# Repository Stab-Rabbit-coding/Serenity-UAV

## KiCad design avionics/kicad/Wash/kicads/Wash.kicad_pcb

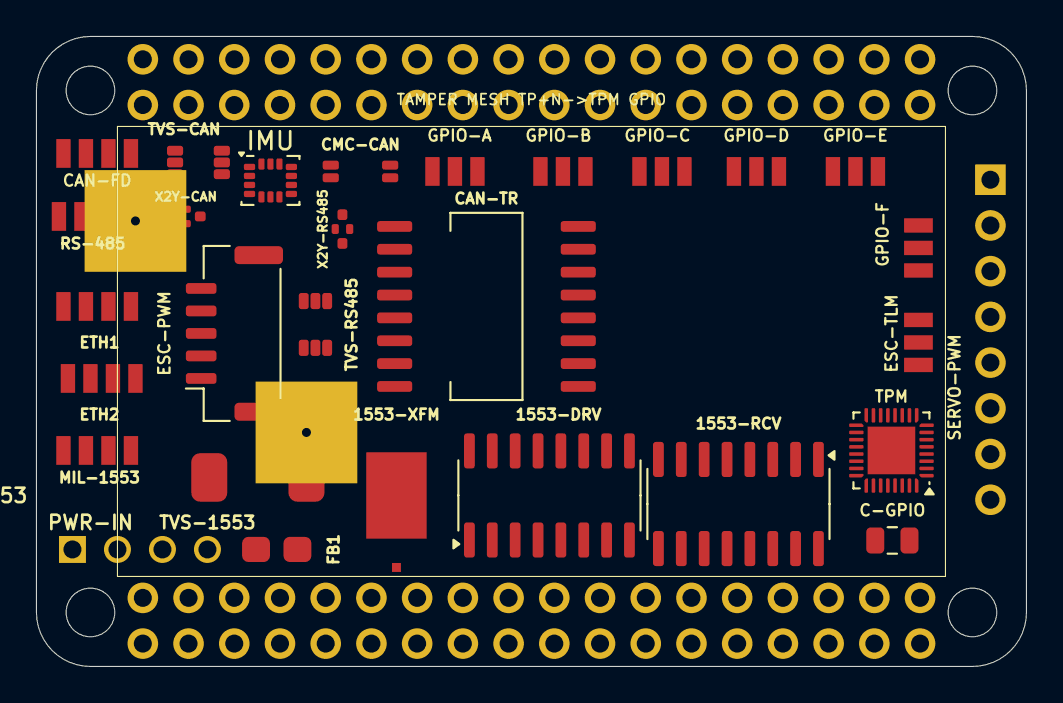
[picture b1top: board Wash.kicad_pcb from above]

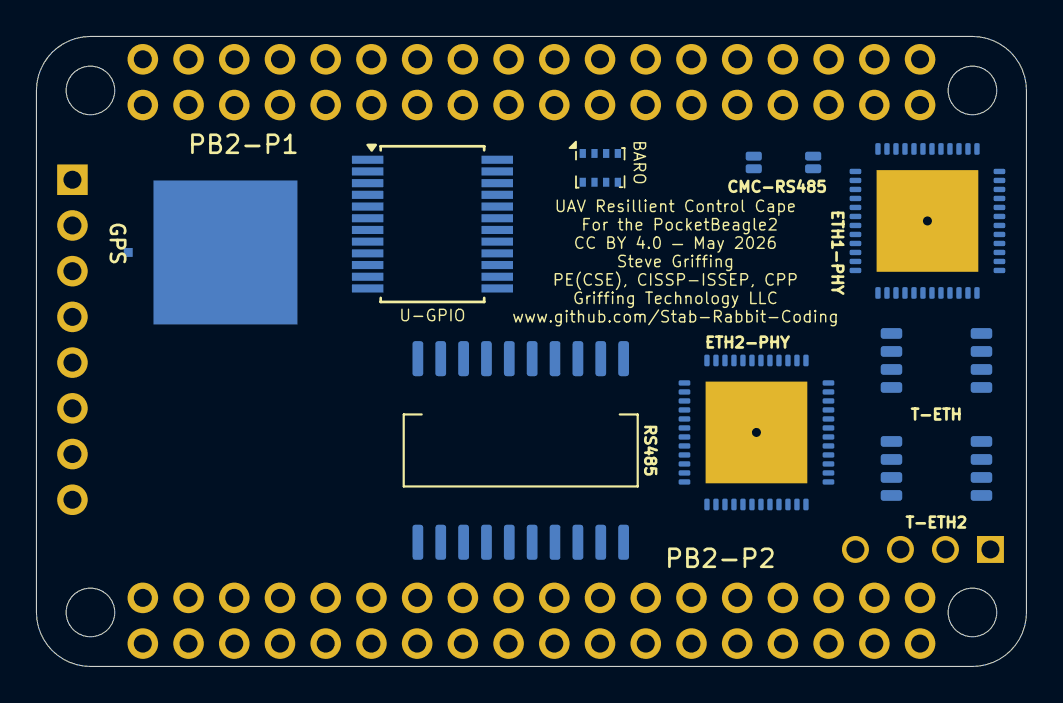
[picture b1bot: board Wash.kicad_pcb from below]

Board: 4 copper layers, 55.0 x 35.0 mm, 40 parts (11 on the bottom side), 90 nets, no tracks yet.

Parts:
1553-DRV: DS26LV31; SOIC-16_3.9x9.9mm_P1.27mm
1553-RCV: DS26LV32; SOIC-16_3.9x9.9mm_P1.27mm
1553-XFM: SM-1553-11; Package
BARO: BMP388; Bosch_LGA-8_2x2.5mm_P0.65mm_ClockwisePinNumbering
C-GPIO: 100nF; C_0805_2012Metric
CAN-FD: JST-GH-4P-CAN; JST_GH_4P
CAN-TR: ISOW1044BDFMR; SOIC-16W_7.5x10.3mm_P1.27mm
CMC-CAN: SRF2012-100Y; Bourns_SRF2012_4T
CMC-RS485: SRF2012-100Y; Bourns_SRF2012_4T
ESC-PWM: JST-GH-5P-ESC; JST_GH_SM05B-GHS-TB_1x05-1MP_P1.25mm_Horizontal
ESC-TLM: JST-GH-3P-ESC-TELEM; JST_GH_3P
ETH1, ETH2: JST-GH-4P-ETH; JST_GH_4P
ETH1-PHY, ETH2-PHY: ADIN1300BCPZ; QFN-48-1EP_7x7mm_P0.5mm_EP5.65x5.65mm
FB1: 742792512; C_0805_2012Metric
GPIO-A: JST-GH-3P-GPIO; JST_GH_3P_V
GPIO-B: JST-GH-3P-GPIO; JST_GH_3P_V
GPIO-C: JST-GH-3P-GPIO; JST_GH_3P_V
GPIO-D: JST-GH-3P-GPIO; JST_GH_3P_V
GPIO-E: JST-GH-3P-GPIO; JST_GH_3P_V
GPIO-F: JST-GH-3P-GPIO; JST_GH_3P_V
GPS: SAM-M10Q-00B; Package
IMU: ICM-42688-P; LGA-14_3x2.5mm_P0.5mm_LayoutBorder3x4y
MIL-1553: JST-GH-4P-1553; JST_GH_4P
PB2-P1: PB2I-P1-2x18; 2x18_P1_Socket
PB2-P2: PB2I-P2-2x18; 2x18_P2_Socket
PWR-IN: Nano-Fit-4P-POWER; Connector_Molex_NanoFit
RS485: ADM2795EBRWZ; SOIC-20W_7.5x12.8mm_P1.27mm
RS-485: JST-GH-4P-RS485; JST_GH_4P
SERVO-PWM: 1x8-SERVO-PWM; Connector_PinHeader_2.54mm
T-ETH, T-ETH2: 749010012A; ETH_XFMR_8P_5x3.5mm
TPM: SLB9670; QFN-32-1EP_4x4mm_P0.4mm_EP2.65x2.65mm
TVS-1553: SMAJ33CA; DO-214AC_SMA
TVS-CAN: PRTR5V0U2X; SOT-363_SC-88
TVS-RS485: PRTR5V0U2X; SOT-363_SC-88
U-GPIO: PCA9555DB; SSOP-24_5.3x8.2mm_P0.65mm
X2Y-CAN, X2Y-RS485: 4.7nF X2Y; X2Y_Cap_4T_0402

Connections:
+3V3: 1553-DRV.16, 1553-RCV.4, 1553-RCV.16, C-GPIO.1, CAN-TR.1, CAN-TR.9, ETH1-PHY.11, ETH1-PHY.20, ETH1-PHY.25, ETH1-PHY.31, ETH1-PHY.40, ETH2-PHY.11, ETH2-PHY.20, ETH2-PHY.25, ETH2-PHY.31, ETH2-PHY.40, GPIO-A.2, GPIO-B.2, GPIO-C.2, GPIO-D.2, GPIO-E.2, GPIO-F.2, IMU.5, IMU.8, PB2-P1.33, PB2-P1.34, RS485.1, RS485.8, RS485.9, TPM.8, TPM.22, U-GPIO.24
+5V: FB1.2, PB2-P1.35, PB2-P2.35, SERVO-PWM.7
+5V_IN: FB1.1, PWR-IN.1, PWR-IN.2
BUS_1553_P: MIL-1553.1, TVS-1553.1
CAN_H_F: CAN-FD.2, CMC-CAN.2, TVS-CAN.1
CAN_L_F: CAN-FD.3, CMC-CAN.3, TVS-CAN.3
CAN_STB: CAN-TR.4, PB2-P1.14
DSHOT0: ESC-PWM.1, PB2-P1.6
DSHOT1: ESC-PWM.2, PB2-P1.5
DSHOT2: ESC-PWM.3, PB2-P1.4
DSHOT3: ESC-PWM.4, PB2-P1.3
DVDD_0P9_ETH1-PHY: ETH1-PHY.4, ETH1-PHY.28, ETH1-PHY.36
DVDD_0P9_ETH2-PHY: ETH2-PHY.4, ETH2-PHY.28, ETH2-PHY.36
ETH2_RXN: ETH2-PHY.15, T-ETH2.8
ETH2_RXP: ETH2-PHY.14, T-ETH2.6
ETH2_TXN: ETH2-PHY.13, T-ETH2.3
ETH2_TXP: ETH2-PHY.12, T-ETH2.1
ETH_RXN: ETH1-PHY.15, T-ETH.8
ETH_RXP: ETH1-PHY.14, T-ETH.6
ETH_TXN: ETH1-PHY.13, T-ETH.3
ETH_TXP: ETH1-PHY.12, T-ETH.1
GND: 1553-DRV.8, 1553-DRV.9, 1553-DRV.12, 1553-DRV.15, 1553-RCV.8, 1553-RCV.12, C-GPIO.2, CAN-TR.6, CAN-TR.10, ESC-PWM.5, ESC-TLM.1, ETH1-PHY.5, ETH1-PHY.41, ETH2-PHY.5, ETH2-PHY.41, GPIO-A.1, GPIO-B.1, GPIO-C.1, GPIO-D.1, GPIO-E.1, GPIO-F.1, GPS.1, IMU.2, IMU.3, IMU.6, IMU.7, IMU.10, IMU.11, MIL-1553.3, PB2-P1.1, PB2-P1.2, PB2-P1.36, PB2-P2.36, PWR-IN.3, PWR-IN.4, RS485.6, RS485.10, SERVO-PWM.8, TPM.2, TPM.9, TPM.23, TPM.32, TPM.33, U-GPIO.2, U-GPIO.3, U-GPIO.12, U-GPIO.21, X2Y-CAN.1, X2Y-CAN.2, X2Y-CAN.3, X2Y-RS485.1, X2Y-RS485.2, X2Y-RS485.3
GND2_CAN: CAN-FD.1, CAN-TR.11, CAN-TR.15, CAN-TR.16, TVS-CAN.2, X2Y-CAN.4
GND2_RS485: RS485.11, RS485.13, RS485.15, RS-485.1, TVS-RS485.2, X2Y-RS485.4
GPIO_EXP_A: GPIO-A.3, U-GPIO.4
GPIO_EXP_B: GPIO-B.3, U-GPIO.5
GPIO_EXP_C: GPIO-C.3, U-GPIO.6
GPIO_EXP_D: GPIO-D.3, U-GPIO.7
GPIO_EXP_E: GPIO-E.3, U-GPIO.8
GPIO_EXP_F: GPIO-F.3, U-GPIO.9
I2C1_SCL: PB2-P1.28, U-GPIO.22
I2C1_SDA: PB2-P1.27, U-GPIO.23
IMU_INT1: IMU.4, PB2-P1.19
IMU_INT2: IMU.9, PB2-P1.18
M1553_N: 1553-DRV.6, 1553-RCV.1, 1553-RCV.6
M1553_P: 1553-DRV.2, 1553-RCV.2, 1553-RCV.7
MCAN0_RX: CAN-TR.5, PB2-P1.15
MCAN0_TX: CAN-TR.3, PB2-P1.16
MDC: ETH1-PHY.23, ETH2-PHY.23
MDIO: ETH1-PHY.24, ETH2-PHY.24
PGND: ESC-PWM.MP, MIL-1553.4, TVS-1553.2
PHY1_INTRN: ETH1-PHY.22, PB2-P2.16
PHY1_RSTN: ETH1-PHY.7, PB2-P2.15
PHY2_INTRN: ETH2-PHY.22, PB2-P2.14
PHY2_RSTN: ETH2-PHY.7, PB2-P2.13
PRU_1553_RX_N: 1553-RCV.5, PB2-P1.7
PRU_1553_RX_P: 1553-RCV.3, PB2-P1.8
PRU_1553_TX_N: 1553-DRV.7, PB2-P1.9
PRU_1553_TX_P: 1553-DRV.1, PB2-P1.10
RMII0_CRS_DV: ETH1-PHY.35, PB2-P2.29
RMII0_REF_CLK: ETH1-PHY.9, PB2-P2.27
RMII0_RXD0: ETH1-PHY.33, PB2-P2.31
RMII0_RXD1: ETH1-PHY.32, PB2-P2.30
RMII0_RX_ER: ETH1-PHY.27, PB2-P2.28
RMII0_TXD0: ETH1-PHY.39, PB2-P2.34
RMII0_TXD1: ETH1-PHY.1, PB2-P2.33
RMII0_TX_EN: ETH1-PHY.37, PB2-P2.32
RMII1_CRS_DV: ETH2-PHY.35, PB2-P2.21
RMII1_REF_CLK: ETH2-PHY.9, PB2-P2.19
RMII1_RXD0: ETH2-PHY.33, PB2-P2.23
RMII1_RXD1: ETH2-PHY.32, PB2-P2.22
RMII1_RX_ER: ETH2-PHY.27, PB2-P2.20
RMII1_TXD0: ETH2-PHY.39, PB2-P2.26
RMII1_TXD1: ETH2-PHY.1, PB2-P2.25
RMII1_TX_EN: ETH2-PHY.37, PB2-P2.24
RS485_A: CMC-RS485.1, RS485.17, RS485.20
RS485_A_F: CMC-RS485.2, RS-485.2, TVS-RS485.1
RS485_B: CMC-RS485.4, RS485.18, RS485.19
RS485_B_F: CMC-RS485.3, RS-485.3, TVS-RS485.3
RS485_DE: PB2-P1.11, RS485.3, RS485.5
RS485_RX: PB2-P1.12, RS485.4
RS485_TX: PB2-P1.13, RS485.2
SERVO0: PB2-P2.8, SERVO-PWM.1
SERVO1: PB2-P2.7, SERVO-PWM.2
SERVO2: PB2-P2.6, SERVO-PWM.3
SERVO3: PB2-P2.5, SERVO-PWM.4
SERVO4: PB2-P2.4, SERVO-PWM.5
SERVO5: PB2-P2.3, SERVO-PWM.6
SPI0_CLK: BARO.6, IMU.13, PB2-P1.25, TPM.19
SPI0_CS_BARO: BARO.7, PB2-P1.22
SPI0_CS_IMU: IMU.12, PB2-P1.26
SPI0_CS_TPM: PB2-P1.21, TPM.20
SPI0_MISO: BARO.3, IMU.1, PB2-P1.23, TPM.24
SPI0_MOSI: BARO.5, IMU.14, PB2-P1.24, TPM.21
TPM_IRQN: PB2-P2.12, TPM.18
TPM_RSTN: PB2-P2.11, TPM.17
UART_ESC_RX: ESC-TLM.3, PB2-P1.29
UART_ESC_TX: ESC-TLM.2, PB2-P1.30
VCC2_CAN: CAN-FD.4, CAN-TR.12, CAN-TR.13, TVS-CAN.5
VCC2_RS485: RS485.12, RS485.16, RS-485.4, TVS-RS485.5

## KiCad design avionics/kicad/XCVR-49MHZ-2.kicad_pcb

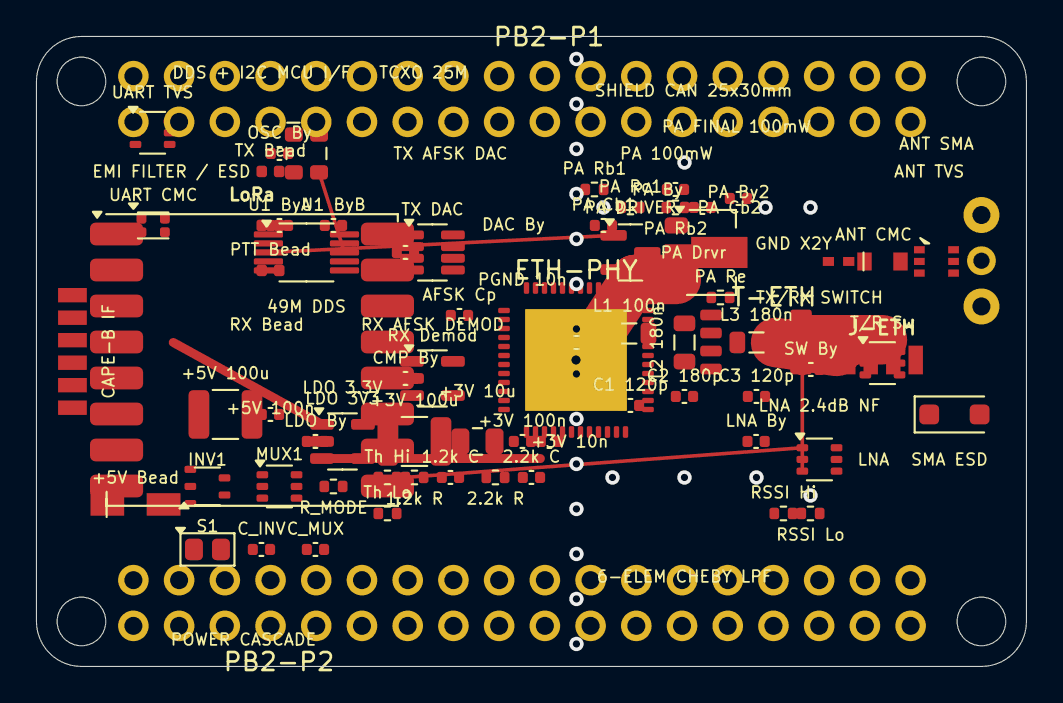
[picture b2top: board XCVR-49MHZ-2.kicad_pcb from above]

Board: 4 copper layers, 55.0 x 35.0 mm, 71 parts (0 on the bottom side), 56 nets.

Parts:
1.2k C: 10nF RX RC Bandpass 1200Hz Cap; C_0402_1005Metric
1.2k R: 13k Ohm RX RC Bandpass 1200Hz; R_0402_1005Metric
2.2k C: 10nF RX RC Bandpass 2200Hz Cap; C_0402_1005Metric
2.2k R: 7.2k Ohm RX RC Bandpass 2200Hz; R_0402_1005Metric
49M DDS: Si5351A-B-GT 49MHz DDS I2C Synthesiser; MSOP-10_3x3mm_P0.5mm
+3V 10n: 10nF C0G 0402 +3V3 VHF 49MHz Bypass; C_0402_1005Metric
+3V 10u: 10uF X5R 0805 +3V3 Mid-freq; C_0805_2012Metric
+3V 100n: 100nF X7R 0402 +3V3 HF Bypass; C_0402_1005Metric
+3V 100u: 100uF 10V X5R 1210 +3V3 Bulk; C_1210_3225Metric
+5V 100n: 100nF X7R 0402 +5V HF Bypass; C_0402_1005Metric
+5V 100u: 100uF 10V X5R 1210 +5V Bulk; C_1210_3225Metric
+5V Bead: 742792512; C_0805_2012Metric
AFSK Cp: 1uF AFSK Audio Coupling DAC→PA; C_0402_1005Metric
ANT CMC: SRF2012-100Y; Bourns_SRF2012
ANT SMA: SMA-EDGE-50R; SMA_Amphenol_132289_EdgeMount
ANT TVS: PRTR5V0U2X; SOT-363_SC-88_MO-178CA
C1 120p: 120pF C0G LPF Shunt-1; C_0402_1005Metric
C2 180p: 180pF C0G LPF Shunt-2; C_0402_1005Metric
C3 120p: 120pF C0G LPF Shunt-3; C_0402_1005Metric
CAPE-B IF: JST-GH-6P-CAPE-B-IF; JST_GH_6P
CMP By: 100nF +3V3 U2B CMP Bypass; C_0402_1005Metric
C_INV: 100nF C0G 0402 INV1 VCC Bypass; C_0402_1005Metric
C_MUX: 100nF C0G 0402 MUX1 VCC Bypass; C_0402_1005Metric
DAC By: 100nF +3V3 U2A DAC Bypass; C_0402_1005Metric
ETH-PHY: ADIN1300BCPZ; QFN-48-1EP_7x7mm_P0.5mm_EP5.65x5.65mm
GND X2Y: 4.7nF_X2Y_C0G; C_0402_1005Metric
INV1: SN74LVC1G04 SOT-23-5 3.3V UART_RX_F->SBUS_OUT; SOT-23-5
J-ETH: JST-GH-4P-ETH; JST_GH_4P
L1 100n: 100nH Coilcraft-0805HQ-101J LPF Series-1; L_0805_2012Metric
L2 180n: 180nH Coilcraft-0805HQ-181J LPF Series-2; L_0805_2012Metric
L3 180n: 180nH Coilcraft-0805HQ-181J LPF Series-3; L_0805_2012Metric
LDO 3V3: MCP1703T-3302 LDO 3.3V 72dB-PSRR@100kHz; SOT-23-5
LDO By: 100nF +3V3 U6 LDO Bypass; C_0402_1005Metric
LNA: MGA-82563 LNA 2.4dB NF 50-6000MHz; SOT-363_SC-70-6
LNA By: 100nF +3V3 U4 LNA Bypass; C_0402_1005Metric
LoRa: RFM95W; HOPERF_RFM9XW_SMD
MUX1: SN74LVC1G157 SC-70-6 2:1MUX UART/SBUS Select; SOT-363_SC-70-6
OSC By: 100nF +3V3 X1 TCXO Bypass; C_0402_1005Metric
PA 100mW: 2N3866 NPN BJT PA Class-AB Final 100mW; SOT-89-3
PA By: 100nF +5V U3 PA VCC Bypass; C_0402_1005Metric
PA By2: 1nF U3B Collector RF Bypass; C_0402_1005Metric
PA Cb1: 100pF DDS-RF Coupling Cap to U3A; C_0402_1005Metric
PA Cb2: 100pF PA Interstage Bypass; C_0402_1005Metric
PA Drvr: MMBT2222A NPN BJT PA Class-A Driver; SOT-23
PA Rb1: 10k Ohm U3A Base Bias Resistor; R_0402_1005Metric
PA Rb2: 1k Ohm U3B Base Bias Resistor; R_0402_1005Metric
PA Rc1: 100 Ohm U3A Collector Load; R_0402_1005Metric
PA Re: 10 Ohm U3B Emitter Degeneration; R_0402_1005Metric
PB2-P1: PB2I-P1-2x18; 2x18_P1_Socket
PB2-P2: PB2I-P2-2x18; 2x18_P2_Socket
PGND 10n: 10nF C0G 0402 GND-PGND Moat Bridge; C_0402_1005Metric
PTT Bead: 742792510 0402 Ferrite Bead 600Ohm@100MHz; L_0402_1005Metric
RSSI Hi: 10k Ohm RSSI Scale Upper; R_0402_1005Metric
RSSI Lo: 10k Ohm RSSI Scale Lower; R_0402_1005Metric
RX Bead: 742792510 0402 Ferrite Bead 600Ohm@100MHz; L_0402_1005Metric
RX Demod: LM393 Comparator RX-AFSK Demodulator; SOT-23-5
R_MODE: 10k Ohm MODE_SEL Pull-Down UART=default; R_0402_1005Metric
S1: SPST-SMD OPEN=UART CLOSED=SBUS; SW_SPST_SMD_2Pin
SMA ESD: SMAJ5.0A Bidirectional TVS 5V Antenna ESD; D_SOD-123F
SW By: 100nF +3V3 U5 Switch Bypass; C_0402_1005Metric
T-ETH: 749010012A; ETH_XFMR_8P_5x3.5mm
T/R Sw: PE4259-63 SPDT TX/RX Switch ≥35dB isolation; SOT-363_SC-70-6
TCXO 25M: TG2520SMN 25MHz TCXO ±0.5ppm; Oscillator_SMD_SeikoEpson_TG2520SMN-xxx-xxxxxx-4Pin_2.5x2.0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
TX Bead: 742792510 0402 Ferrite Bead 600Ohm@100MHz; L_0402_1005Metric
TX DAC: MCP4921 12-bit SPI DAC TX-AFSK Audio; SOT-23-8
Th Hi: 10k Ohm LM393 Threshold Upper; R_0402_1005Metric
Th Lo: 10k Ohm LM393 Threshold Lower; R_0402_1005Metric
U1 ByA: 100nF +3V3 U1-VDDA Bypass; C_0402_1005Metric
U1 ByB: 100nF +3V3 U1-VDD Bypass; C_0402_1005Metric
UART CMC: SRF2012-100Y CMC UART TX/RX Pair 10uH; SRF2012_2012Metric
UART TVS: PRTR5V0U2X Dual TVS 5.5V UART-TX/RX ESD; SOT-363_SC-70-6

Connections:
+3V3: 49M DDS.1, 49M DDS.10, +3V 10n.1, +3V 10u.1, +3V 100n.1, +3V 100u.1, CAPE-B IF.6, CMP By.1, C_INV.1, C_MUX.1, DAC By.1, INV1.4, LDO 3V3.3, LDO 3V3.4, LDO By.1, LNA.4, LNA By.1, MUX1.4, OSC By.1, PB2-P1.33, PB2-P1.34, RX Demod.2, S1.1, SW By.1, TCXO 25M.1, TCXO 25M.4, TX DAC.1, TX DAC.6, Th Hi.1, U1 ByA.1, U1 ByB.1
+5V: +5V Bead.1, PB2-P1.35, PB2-P2.35
+5V_FILT: +5V 100n.1, +5V 100u.1, +5V Bead.2, LDO 3V3.1, PA By.1, PA Rb1.1, PA Rc1.1
AFSK_IN: AFSK Cp.2, RX Demod.1
AFSK_OUT: AFSK Cp.1, TX DAC.7
ANT: ANT CMC.1, ANT CMC.2, ANT SMA.1, ANT TVS.2, SMA ESD.1
COMP_IN: 1.2k C.1, 1.2k R.2, 2.2k C.1, 2.2k R.2, RX Demod.3, Th Lo.1
DDS_CLK: 49M DDS.6, TX DAC.3
DDS_DAT: 49M DDS.7, TX DAC.4
DDS_RF: 49M DDS.3, PA Cb1.1, PA Drvr.1, PA Rb1.2
EMMA_ETH_LINE_RXN: J-ETH.4, T-ETH.8
EMMA_ETH_LINE_RXP: J-ETH.3, T-ETH.7
EMMA_ETH_LINE_TXN: J-ETH.2, T-ETH.6
EMMA_ETH_LINE_TXP: J-ETH.1, T-ETH.5
EMMA_ETH_RXN: ETH-PHY.5, T-ETH.4
EMMA_ETH_RXP: ETH-PHY.4, T-ETH.3
EMMA_ETH_TXN: ETH-PHY.2, T-ETH.2
EMMA_ETH_TXP: ETH-PHY.1, T-ETH.1
GND: 1.2k C.2, 2.2k C.2, 49M DDS.2, 49M DDS.4, 49M DDS.5, 49M DDS.9, +3V 10n.2, +3V 10u.2, +3V 100n.2, +3V 100u.2, +5V 100n.2, +5V 100u.2, ANT SMA.2, ANT SMA.3, ANT TVS.1, ANT TVS.3, ANT TVS.4, ANT TVS.6, C1 120p.2, C2 180p.2, C3 120p.2, CAPE-B IF.1, CMP By.2, C_INV.2, C_MUX.2, DAC By.2, ETH-PHY.3, ETH-PHY.6, ETH-PHY.10, ETH-PHY.11, ETH-PHY.12, ETH-PHY.49, GND X2Y.1, GND X2Y.2, INV1.2, LDO 3V3.2, LDO 3V3.5, LDO By.2, LNA.5, LNA.6, LNA By.2, MUX1.2, OSC By.2, PA 100mW.2, PA By.2, PA By2.2, PA Cb2.2, PA Drvr.2, PA Re.2, PB2-P1.1, PB2-P1.2, PB2-P1.36, PB2-P2.36, PGND 10n.1, PGND 10n.2, RSSI Lo.2, RX Demod.4, RX Demod.5, R_MODE.2, SMA ESD.2, SW By.2, T/R Sw.2, T/R Sw.6, TCXO 25M.2, TX DAC.5, TX DAC.8, Th Hi.2, Th Lo.2, U1 ByA.2, U1 ByB.2, UART TVS.1, UART TVS.3, UART TVS.4, UART TVS.6
GND2_ETH: ETH-PHY.21, ETH-PHY.22, ETH-PHY.25, ETH-PHY.34, ETH-PHY.36
LORA_RESETN: LoRa.2, PB2-P1.19
MDC: ETH-PHY.19, PB2-P2.18
MDIO: ETH-PHY.18, PB2-P2.17
MODE_SEL: MUX1.5, R_MODE.1, S1.2
PA_INT: PA 100mW.1, PA Cb1.2, PA Cb2.1, PA Drvr.3, PA Rb2.1, PA Rb2.2, PA Rc1.2
PHY2_INTRN: ETH-PHY.20, PB2-P2.14
PHY2_RSTN: ETH-PHY.35, PB2-P2.13
PTT_N: CAPE-B IF.4, PTT Bead.1, PTT Bead.2, T/R Sw.4
RF_FILT: C3 120p.1, L3 180n.2, T/R Sw.5
RF_LPF_N1: C1 120p.1, L1 100n.2, L2 180n.1
RF_LPF_N2: C2 180p.1, L2 180n.2, L3 180n.1
RF_RX: LNA.3, T/R Sw.3
RF_TX: ANT TVS.5, L1 100n.1, PA 100mW.3, PA By2.1
RMII1_CRS_DV: ETH-PHY.32, PB2-P2.21
RMII1_REF_CLK: ETH-PHY.29, PB2-P2.19
RMII1_RXD0: ETH-PHY.30, PB2-P2.23
RMII1_RXD1: ETH-PHY.31, PB2-P2.22
RMII1_RX_ER: ETH-PHY.33, PB2-P2.20
RMII1_TXD0: ETH-PHY.28, PB2-P2.26
RMII1_TXD1: ETH-PHY.27, PB2-P2.25
RMII1_TX_EN: ETH-PHY.26, PB2-P2.24
RSSI_ANA: CAPE-B IF.5, RSSI Hi.2, RSSI Lo.1
RSSI_RAW: LNA.2, RSSI Hi.1
RX_LNA: 1.2k R.1, 2.2k R.1, LNA.1
SBUS_OUT: INV1.3, MUX1.6
SPI1_CLK: LoRa.12, PB2-P1.25
SPI1_CS_LORA: LoRa.13, PB2-P1.26
SPI1_MISO: LoRa.10, PB2-P1.23
SPI1_MOSI: LoRa.11, PB2-P1.24
TCXO_OUT: 49M DDS.8, TCXO 25M.3
UART_RX: CAPE-B IF.3, UART CMC.4, UART TVS.5
UART_RX_F: INV1.1, MUX1.1, RX Bead.1, RX Bead.2
UART_RX_MUX: MUX1.3, UART CMC.3
UART_TX: CAPE-B IF.2, UART CMC.1, UART TVS.2
UART_TX_F: TX Bead.1, TX Bead.2, UART CMC.2
VCC2_ETH: ETH-PHY.7, ETH-PHY.8, ETH-PHY.9, ETH-PHY.40, ETH-PHY.41

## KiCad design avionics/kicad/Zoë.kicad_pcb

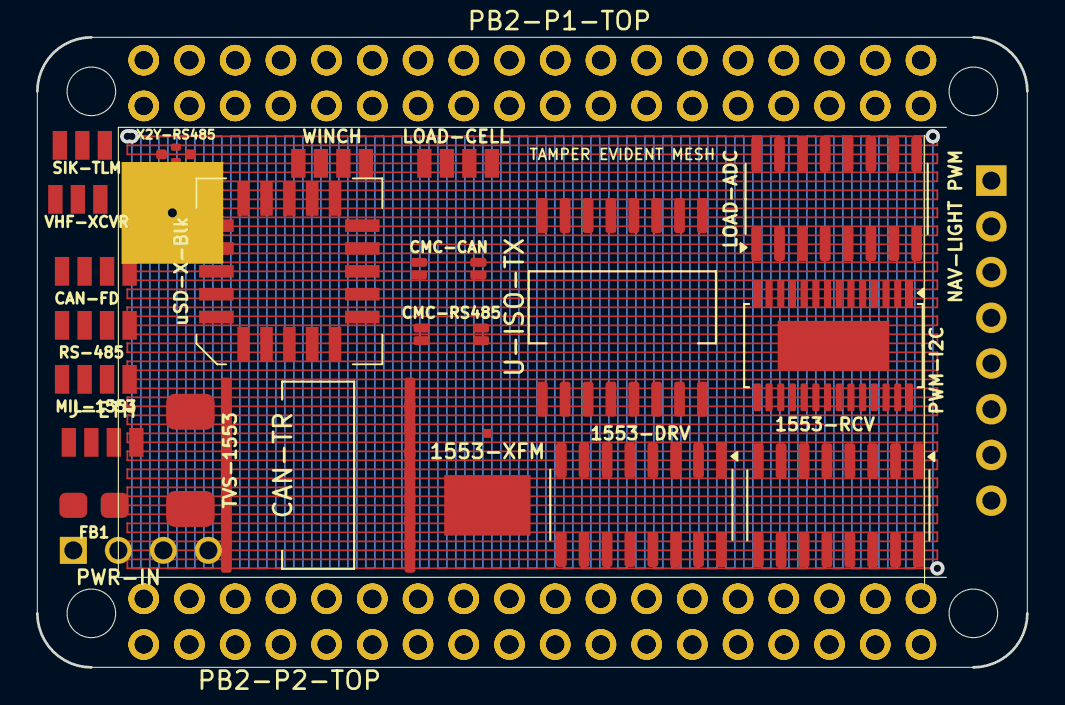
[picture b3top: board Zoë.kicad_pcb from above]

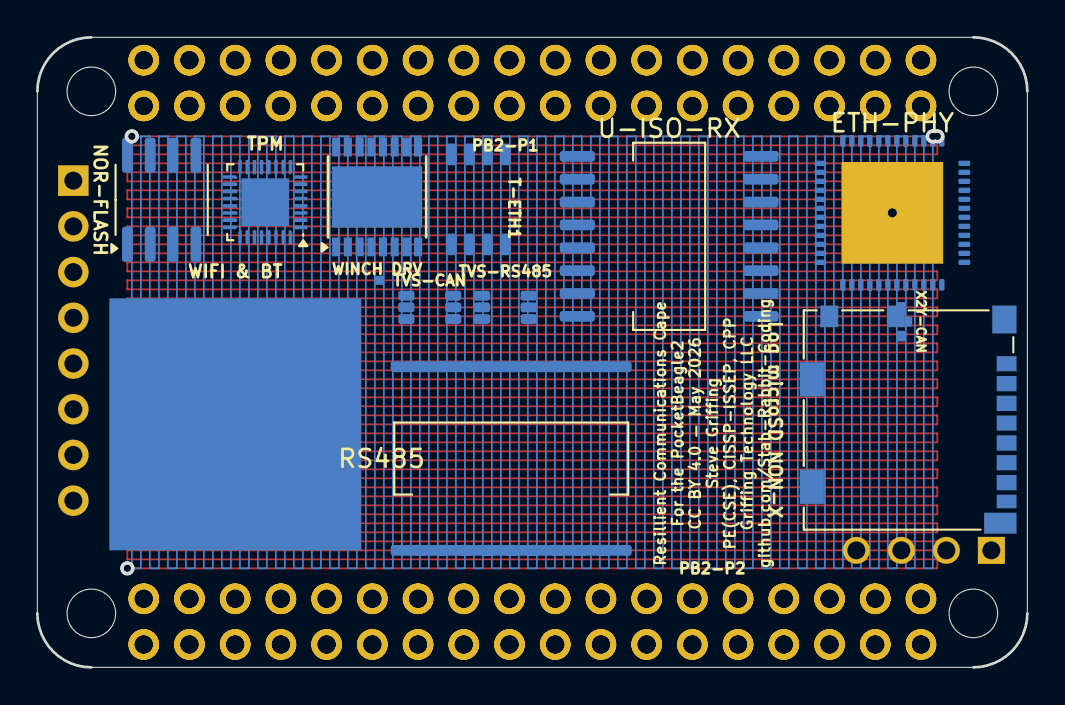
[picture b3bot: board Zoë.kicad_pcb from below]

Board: 4 copper layers, 55.0 x 35.0 mm, 39 parts (14 on the bottom side), 85 nets.

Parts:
1553-DRV: DS26LV31; SOIC-16_3.9x9.9mm_P1.27mm
1553-RCV: DS26LV32; SOIC-16_3.9x9.9mm_P1.27mm
1553-XFM: SM-1553-11; Package
CAN-FD: JST-GH-4P-CAN; JST_GH_4P
CAN-TR: ISOW1044BDFMR; SOIC-16W_7.5x10.3mm_P1.27mm
CMC-CAN: SRF2012-100Y; Bourns_SRF2012_4T
CMC-RS485: SRF2012-100Y; Bourns_SRF2012_4T
ETH-PHY: ADIN1300BCPZ; QFN-48-1EP_7x7mm_P0.5mm_EP5.65x5.65mm
FB1: 742792512; C_0805_2012Metric
J-ETH: JST-GH-4P-ETH; JST_GH_4P
LOAD-ADC: HX711; SOIC-16_3.9x9.9mm_P1.27mm
LOAD-CELL: JST-GH-4P-LOAD-CELL; JST_GH_4P
Log microSD NON-X: microSD-Log; microSD_HC_Molex_104031-0811
MIL-1553: JST-GH-4P-1553; JST_GH_4P
NAV-LIGHT PWM: 1x8-NavLight-PWM; Connector_PinHeader_2.54mm
NOR-FLASH: W25Q128JV; SOIC-8_3.9x4.9mm_P1.27mm
PB2-P1, PB2-P1-TOP: PB2I-P1-2x18; 2x18_P1_Socket
PB2-P2, PB2-P2-TOP: PB2I-P2-2x18; 2x18_P2_Socket
PWM-I2C: PCA9685; HTSSOP-28-1EP_4.4x9.7mm_P0.65mm_EP2.75x6.2mm
PWR-IN: Nano-Fit-4P-POWER; Connector_Molex_NanoFit
RS485: ADM2795EBRWZ; SOIC-20W_7.5x12.8mm_P1.27mm
RS-485: JST-GH-4P-RS485; JST_GH_4P
SIK-TLM: JST-GH-3P-SiK; JST_GH_3P
T-ETH1: 749010012A; ETH_XFMR_8P_5x3.5mm
TPM: SLB9670; QFN-32-1EP_4x4mm_P0.4mm_EP2.65x2.65mm
TVS-1553: SMAJ33CA; DO-214AC_SMA
TVS-CAN: PRTR5V0U2X; SOT-363_SC-88
TVS-RS485: PRTR5V0U2X; SOT-363_SC-88
U-ISO-RX: ISO7642FDWRR; SOIC-16W_7.5x10.3mm_P1.27mm
U-ISO-TX: ISO7642FDWRR; SOIC-16W_7.5x10.3mm_P1.27mm
VHF-XCVR: JST-GH-3P-RCRS; JST_GH_3P
WIFI & BT: WL1837MOD; RF_Module
WINCH: JST-GH-4P-WINCH; JST_GH_4P
WINCH DRV: DRV8833; HTSSOP-16-1EP_4.4x5mm_P0.65mm_EP3.4x5mm
X2Y-CAN, X2Y-RS485: 4.7nF X2Y; X2Y_Cap_4T_0402
uSD-X-Blk: ATF16V8BQL; PLCC-20

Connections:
+3V3: CAN-TR.1, PB2-P1.33, PB2-P1.34, PB2-P1-TOP.33, PB2-P1-TOP.34, RS485.1, U-ISO-RX.16, U-ISO-TX.1
+5V: FB1.1, FB1.2, PB2-P1.35, PB2-P1-TOP.35, PB2-P2.35, PB2-P2-TOP.35
CAN_H: CAN-TR.9, CMC-CAN.1, CMC-CAN.3, TVS-CAN.1
CAN_L: CAN-TR.10, CMC-CAN.2, CMC-CAN.4, TVS-CAN.3
CAN_STB: CAN-TR.3, PB2-P1.12, PB2-P1-TOP.12
ETH_LINE_RXN: J-ETH.4, T-ETH1.8
ETH_LINE_RXP: J-ETH.3, T-ETH1.7
ETH_LINE_TXN: J-ETH.2, T-ETH1.6
ETH_LINE_TXP: J-ETH.1, T-ETH1.5
ETH_RXN: ETH-PHY.5, T-ETH1.4
ETH_RXP: ETH-PHY.4, T-ETH1.3
ETH_TXN: ETH-PHY.2, T-ETH1.2
ETH_TXP: ETH-PHY.1, T-ETH1.1
GND: CAN-TR.8, ETH-PHY.3, ETH-PHY.6, ETH-PHY.10, ETH-PHY.11, ETH-PHY.12, ETH-PHY.49, PB2-P1.1, PB2-P1.2, PB2-P1.36, PB2-P1-TOP.1, PB2-P1-TOP.2, PB2-P1-TOP.36, PB2-P2.36, PB2-P2-TOP.36, RS485.2, RS485.7, RS485.8, TVS-1553.1, U-ISO-RX.9, U-ISO-TX.8, X2Y-CAN.1, X2Y-CAN.2, X2Y-CAN.3, X2Y-RS485.1, X2Y-RS485.2, X2Y-RS485.3
GND2_CAN: CAN-TR.12, CAN-TR.13, TVS-CAN.2, X2Y-CAN.4
GND2_ETH: ETH-PHY.21, ETH-PHY.22, ETH-PHY.25, ETH-PHY.34, ETH-PHY.36, U-ISO-RX.8, U-ISO-TX.9
GND2_RS485: RS485.12, RS485.13, RS485.18, RS485.19, TVS-RS485.2, X2Y-RS485.4
I2C0_SCL: PB2-P1.4, PB2-P1-TOP.4, PWM-I2C.24
I2C0_SDA: PB2-P1.3, PB2-P1-TOP.3, PWM-I2C.22
LOAD_CELL_DOUT: PB2-P2.7, PB2-P2-TOP.7
LOAD_CELL_SCK: LOAD-ADC.16, PB2-P2.8, PB2-P2-TOP.8
LORA_DIO0: PB2-P1.20, PB2-P1-TOP.20
LORA_RESETN: PB2-P1.19, PB2-P1-TOP.19
MCAN1_RX: CAN-TR.4, PB2-P1.13, PB2-P1-TOP.13
MCAN1_TX: CAN-TR.2, PB2-P1.14, PB2-P1-TOP.14
MDC: ETH-PHY.19, PB2-P2.18, PB2-P2-TOP.18, U-ISO-TX.6, U-ISO-TX.11
MDIO: ETH-PHY.18, PB2-P2.17, PB2-P2-TOP.17, U-ISO-RX.7, U-ISO-RX.10
PHY1_INTRN: ETH-PHY.20, PB2-P2.16, PB2-P2-TOP.16, U-ISO-RX.6, U-ISO-RX.11
PHY1_RSTN: ETH-PHY.35, PB2-P2.15, PB2-P2-TOP.15, U-ISO-TX.7, U-ISO-TX.10
PHY2_INTRN: PB2-P2.14, PB2-P2-TOP.14
PHY2_RSTN: PB2-P2.13, PB2-P2-TOP.13
PRU_1553_RX_N: 1553-RCV.13, PB2-P1.5, PB2-P1-TOP.5
PRU_1553_RX_P: PB2-P1.6, PB2-P1-TOP.6
PRU_1553_TX_N: 1553-DRV.6, PB2-P1.7, PB2-P1-TOP.7
PRU_1553_TX_P: 1553-DRV.10, PB2-P1.8, PB2-P1-TOP.8
PWM_CH0: PB2-P2.6, PB2-P2-TOP.6, uSD-X-Blk.6
PWM_CH1: PB2-P2.5, PB2-P2-TOP.5, PWM-I2C.11, uSD-X-Blk.5
PWM_CH2: PB2-P2.4, PB2-P2-TOP.4, PWM-I2C.10, uSD-X-Blk.4
PWM_CH3: PB2-P2.3, PB2-P2-TOP.3, PWM-I2C.9, uSD-X-Blk.3
RMII0_CRS_DV: ETH-PHY.32, PB2-P2.29, PB2-P2-TOP.29, U-ISO-RX.4, U-ISO-RX.13
RMII0_REF_CLK: ETH-PHY.29, PB2-P2.27, PB2-P2-TOP.27, U-ISO-TX.2, U-ISO-TX.15
RMII0_RXD0: ETH-PHY.30, PB2-P2.31, PB2-P2-TOP.31, U-ISO-RX.2, U-ISO-RX.15
RMII0_RXD1: ETH-PHY.31, PB2-P2.30, PB2-P2-TOP.30, U-ISO-RX.3, U-ISO-RX.14
RMII0_RX_ER: ETH-PHY.33, PB2-P2.28, PB2-P2-TOP.28, U-ISO-RX.5, U-ISO-RX.12
RMII0_TXD0: ETH-PHY.28, PB2-P2.34, PB2-P2-TOP.34, U-ISO-TX.3, U-ISO-TX.14
RMII0_TXD1: ETH-PHY.27, PB2-P2.33, PB2-P2-TOP.33, U-ISO-TX.4, U-ISO-TX.13
RMII0_TX_EN: ETH-PHY.26, PB2-P2.32, PB2-P2-TOP.32, U-ISO-TX.5, U-ISO-TX.12
RMII1_CRS_DV: PB2-P2.21, PB2-P2-TOP.21
RMII1_REF_CLK: PB2-P2.19, PB2-P2-TOP.19
RMII1_RXD0: PB2-P2.23, PB2-P2-TOP.23
RMII1_RXD1: PB2-P2.22, PB2-P2-TOP.22
RMII1_RX_ER: PB2-P2.20, PB2-P2-TOP.20
RMII1_TXD0: PB2-P2.26, PB2-P2-TOP.26
RMII1_TXD1: PB2-P2.25, PB2-P2-TOP.25
RMII1_TX_EN: PB2-P2.24, PB2-P2-TOP.24
RS485_A: CMC-RS485.1, CMC-RS485.3, RS485.14, TVS-RS485.1
RS485_B: CMC-RS485.2, CMC-RS485.4, RS485.15, TVS-RS485.3
RS485_DE: PB2-P1.9, PB2-P1-TOP.9, RS485.4, RS485.5
RS485_RX: PB2-P1.10, PB2-P1-TOP.10, RS485.6
RS485_TX: PB2-P1.11, PB2-P1-TOP.11, RS485.3
SDIO_CLK: Log microSD NON-X.6, PB2-P1.32, PB2-P1-TOP.32
SDIO_CMD: Log microSD NON-X.8, PB2-P1.31, PB2-P1-TOP.31
SDIO_D0: Log microSD NON-X.4, PB2-P1.30, PB2-P1-TOP.30
SDIO_D1: PB2-P1.29, PB2-P1-TOP.29
SDIO_D2: Log microSD NON-X.3, PB2-P1.28, PB2-P1-TOP.28
SDIO_D3: PB2-P1.27, PB2-P1-TOP.27
SERVO6: PB2-P2.2, PB2-P2-TOP.2
SERVO7: PB2-P2.1, PB2-P2-TOP.1, uSD-X-Blk.15
SPI1_CLK: NOR-FLASH.2, PB2-P1.25, PB2-P1-TOP.25, TPM.23
SPI1_CS_LORA: PB2-P1.26, PB2-P1-TOP.26
SPI1_CS_NOR: NOR-FLASH.3, PB2-P1.22, PB2-P1-TOP.22
SPI1_CS_TPM: PB2-P1.21, PB2-P1-TOP.21, TPM.28
SPI1_MISO: NOR-FLASH.6, PB2-P1.23, PB2-P1-TOP.23, TPM.22
SPI1_MOSI: NOR-FLASH.5, PB2-P1.24, PB2-P1-TOP.24, TPM.21
TPM_IRQN: PB2-P2.12, PB2-P2-TOP.12, TPM.24
TPM_RSTN: PB2-P2.11, PB2-P2-TOP.11, TPM.1
UART_RCRS_RX: PB2-P1.15, PB2-P1-TOP.15
UART_RCRS_TX: PB2-P1.16, PB2-P1-TOP.16
UART_SIK_RX: PB2-P1.17, PB2-P1-TOP.17
UART_SIK_TX: PB2-P1.18, PB2-P1-TOP.18
VCC2_CAN: CAN-TR.14, TVS-CAN.5
VCC2_ETH: ETH-PHY.7, ETH-PHY.8, ETH-PHY.9, ETH-PHY.40, ETH-PHY.41, U-ISO-RX.1, U-ISO-TX.16
VCC2_RS485: RS485.11, RS485.20, TVS-RS485.5
WINCH_IN1: PB2-P2.10, PB2-P2-TOP.10, WINCH DRV.5
WINCH_IN2: PB2-P2.9, PB2-P2-TOP.9, WINCH DRV.8

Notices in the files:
avionics/kicad/Wash/kicads/Wash.kicad_pcb:
CC BY 4.0 creativecommons.org/licenses/by/4.0
Hull: misubisu CC BY 4.0 | Nozzle: BamJr CC BY 4.0 | Firefly/Serenity fan-work, not officially licensed
CC BY 4.0 — May 2026
avionics/kicad/XCVR-49MHZ-2.kicad_pcb:
CC BY 4.0 creativecommons.org/licenses/by/4.0 — Steve Griffing PE(CSE) CISSP-ISSEP CPP
Hull: Peter Farell CC BY 4.0 | Firefly/Serenity fan-work, not officially licensed
CC BY 4.0 — June 2026
